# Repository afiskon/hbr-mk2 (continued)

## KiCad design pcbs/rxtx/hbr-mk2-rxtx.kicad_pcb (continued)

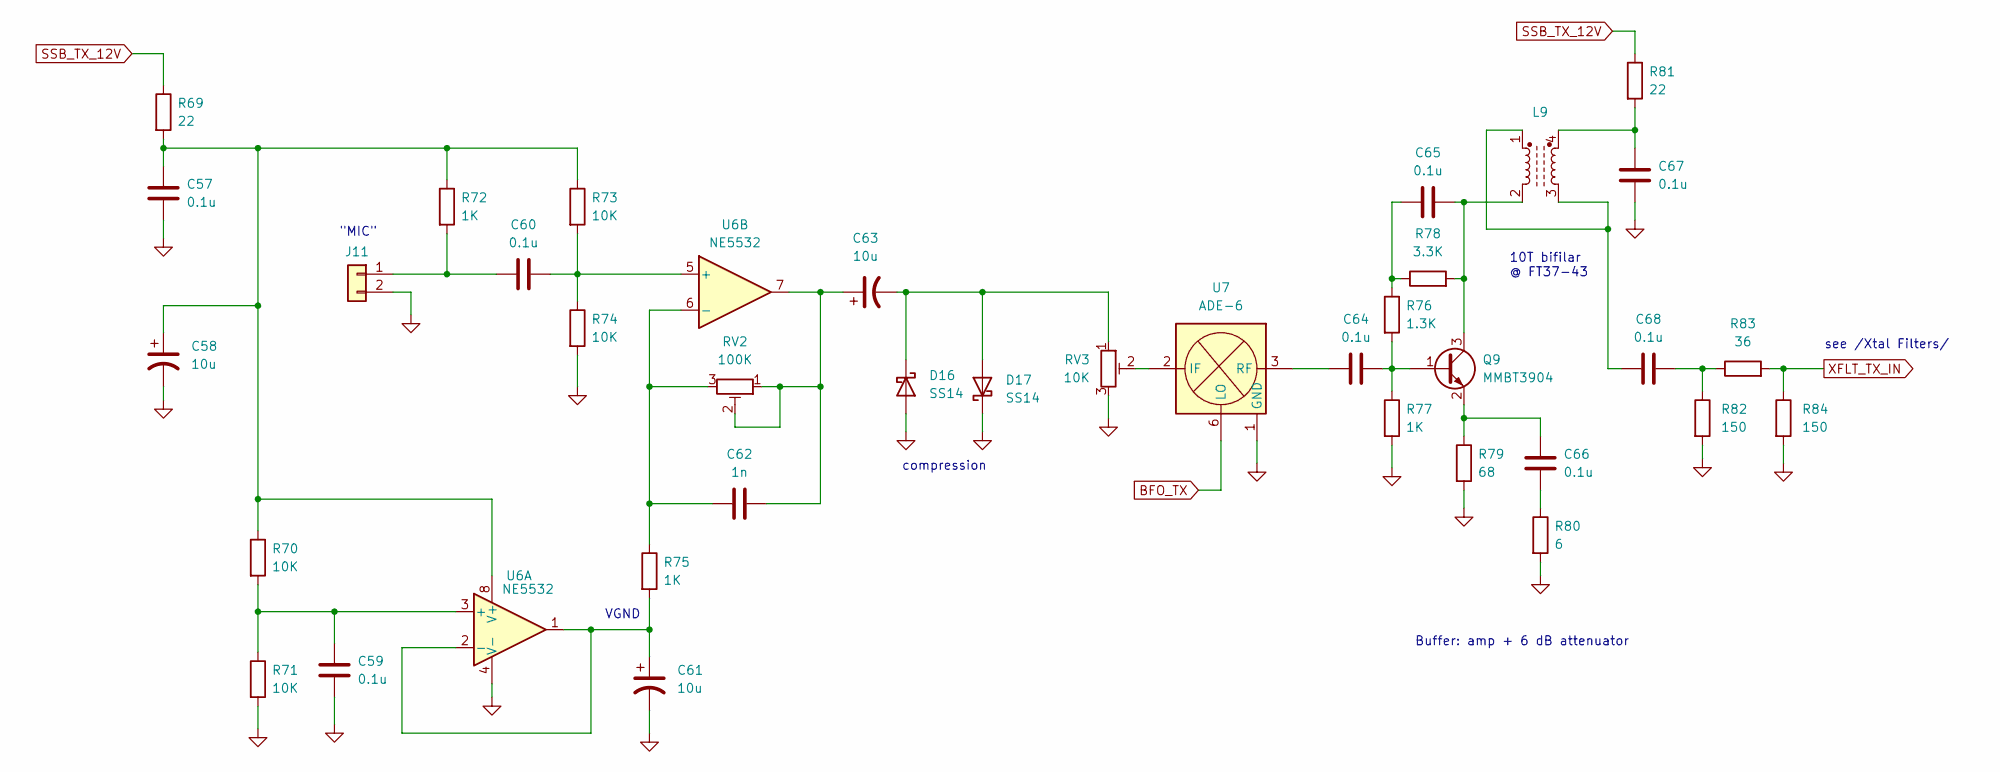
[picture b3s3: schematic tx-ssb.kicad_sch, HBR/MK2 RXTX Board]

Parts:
C57, C59, C60, C64, C65, C66, C67, C68: 0.1u; C_0805_2012Metric_Pad1.18x1.45mm_HandSolder
C58, C61, C63: 10u; CP_Elec_4x5.4
C62: 1n; C_0805_2012Metric_Pad1.18x1.45mm_HandSolder
D16, D17: SS14; D_SMA_Handsoldering
J11: Conn_01x02; PinHeader_1x02_P2.54mm_Vertical
L9: FT37-43; DIP-4_W7.62mm
Q9: MMBT3904; SOT-23
R69, R81: 22; R_0805_2012Metric_Pad1.20x1.40mm_HandSolder
R70, R71, R73, R74: 10K; R_0805_2012Metric_Pad1.20x1.40mm_HandSolder
R72, R75, R77: 1K; R_0805_2012Metric_Pad1.20x1.40mm_HandSolder
R76: 1.3K; R_0805_2012Metric_Pad1.20x1.40mm_HandSolder
R78: 3.3K; R_0805_2012Metric_Pad1.20x1.40mm_HandSolder
R79: 68; R_0805_2012Metric_Pad1.20x1.40mm_HandSolder
R80: 6; R_0805_2012Metric_Pad1.20x1.40mm_HandSolder
R82, R84: 150; R_0805_2012Metric_Pad1.20x1.40mm_HandSolder
R83: 36; R_0805_2012Metric_Pad1.20x1.40mm_HandSolder
RV2: 100K; Potentiometer_Bourns_3296W_Vertical
RV3: 10K; Potentiometer_Bourns_3296W_Vertical
U6: NE5532; SOIC-8_5.23x5.23mm_P1.27mm
U7: ADE-6; Mini-Circuits_CD542_LandPatternPL-052

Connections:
BFO_TX: U7.6 (LO); also elsewhere on the board
GND: C57.2, C58.2, C59.2, C61.2, C67.1, D16.2 (A), D17.1 (K), J11.2, R71.2, R74.2, R77.2, R79.2, R80.2, R82.2, R84.2, RV3.3, U6.4 (V-), U7.1 (GND), U7.4 (GND), U7.5 (GND); also elsewhere on the board
unnamed: C62.2, C63.1, RV2.1, RV2.2, U6.7
unnamed: C65.1, R76.1, R78.1
unnamed: C66.1, R80.1
unnamed: C67.2, L9.4, R81.2
unnamed: C68.1, L9.1, L9.3
unnamed: C68.2, R82.1, R83.1
unnamed: C63.2, D16.1 (K), D17.2 (A), RV3.1
unnamed: C60.1, J11.1, R72.2
unnamed: C64.2, Q9.1 (B), R76.2, R77.1
unnamed: C65.2, L9.2, Q9.3 (C), R78.2
unnamed: C66.2, Q9.2 (E), R79.1
unnamed: C59.1, R70.2, R71.1, U6.3 (+)
unnamed: C61.1, R75.2, U6.1, U6.2 (-)
unnamed: C60.2, R73.2, R74.1, U6.5 (+)
unnamed: C62.1, R75.1, RV2.3, U6.6 (-)
unnamed: C57.1, C58.1, R69.2, R70.1, R72.1, R73.1, U6.8 (V+)
unnamed: RV3.2, U7.2 (IF)
unnamed: C64.1, U7.3 (RF)
SSB_TX_12V: R69.1, R81.1; also elsewhere on the board
XFLT_TX_IN: R83.2, R84.1; also elsewhere on the board

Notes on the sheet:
see /Xtal Filters/
10T bifilar @ FT37-43
Buffer: amp + 6 dB attenuator
VGND
"MIC"
compression

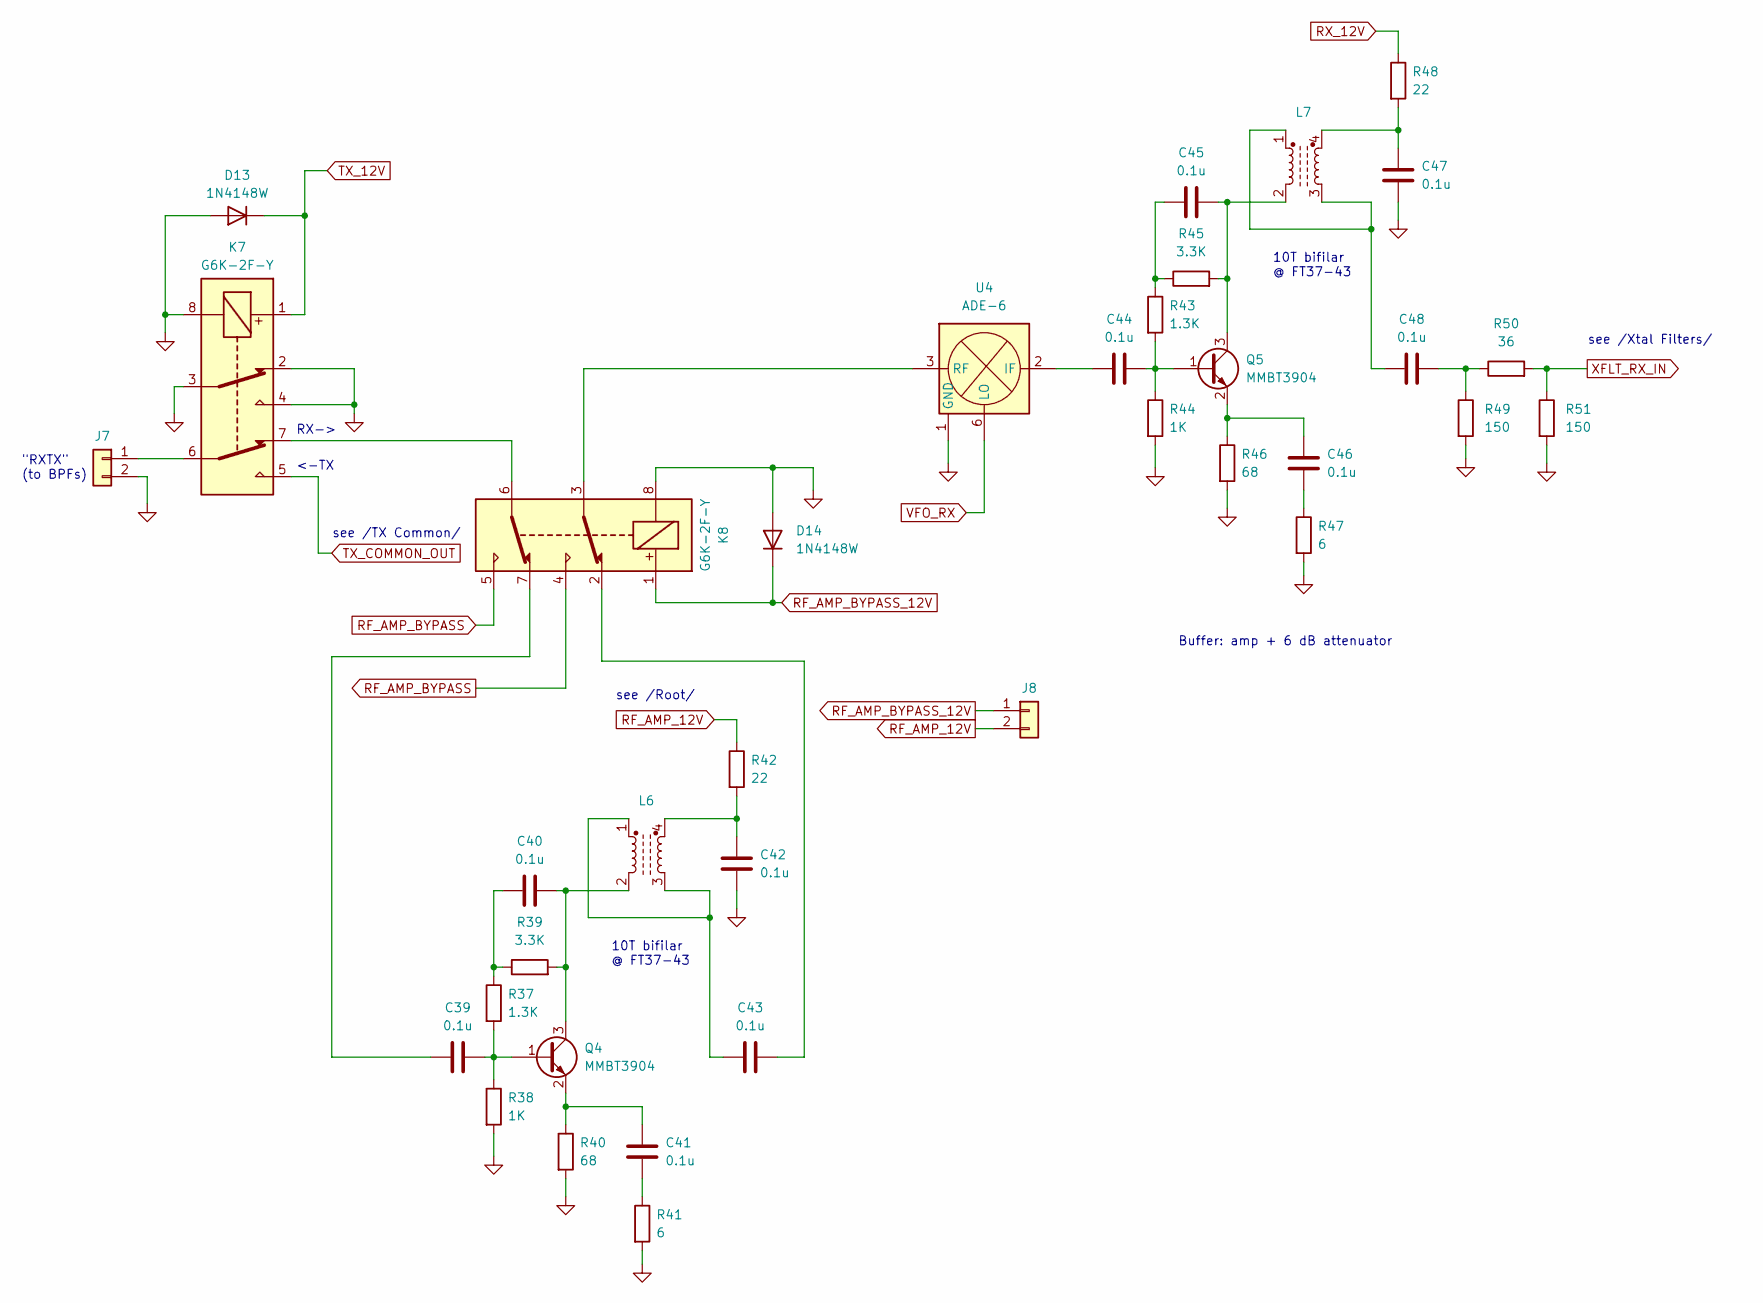
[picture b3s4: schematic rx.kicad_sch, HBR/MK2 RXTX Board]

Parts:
C39, C40, C41, C42, C43, C44, C45, C46, C47, C48: 0.1u; C_0805_2012Metric_Pad1.18x1.45mm_HandSolder
D13, D14: 1N4148W; D_SOD-123
J7, J8: Conn_01x02; PinHeader_1x02_P2.54mm_Vertical
K7, K8: G6K-2F-Y; Relay_DPDT_Omron_G6K-2F-Y
L6, L7: FT37-43; DIP-4_W7.62mm
Q4, Q5: MMBT3904; SOT-23
R37, R43: 1.3K; R_0805_2012Metric_Pad1.20x1.40mm_HandSolder
R38, R44: 1K; R_0805_2012Metric_Pad1.20x1.40mm_HandSolder
R39, R45: 3.3K; R_0805_2012Metric_Pad1.20x1.40mm_HandSolder
R40, R46: 68; R_0805_2012Metric_Pad1.20x1.40mm_HandSolder
R41, R47: 6; R_0805_2012Metric_Pad1.20x1.40mm_HandSolder
R42, R48: 22; R_0805_2012Metric_Pad1.20x1.40mm_HandSolder
R49, R51: 150; R_0805_2012Metric_Pad1.20x1.40mm_HandSolder
R50: 36; R_0805_2012Metric_Pad1.20x1.40mm_HandSolder
U4: ADE-6; Mini-Circuits_CD542_LandPatternPL-052

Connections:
GND: C42.1, C47.1, D13.2 (A), D14.2 (A), J7.2, K7.2, K7.3, K7.4, K7.8, K8.8, R38.2, R40.2, R41.2, R44.2, R46.2, R47.2, R49.2, R51.2, U4.1 (GND), U4.4 (GND), U4.5 (GND); also elsewhere on the board
unnamed: C39.1, K8.7
unnamed: C40.1, R37.1, R39.1
unnamed: C41.1, R41.1
unnamed: C42.2, L6.4, R42.2
unnamed: C43.1, L6.1, L6.3
unnamed: C43.2, K8.2
unnamed: C45.1, R43.1, R45.1
unnamed: C46.1, R47.1
unnamed: C47.2, L7.4, R48.2
unnamed: C48.1, L7.1, L7.3
unnamed: C48.2, R49.1, R50.1
unnamed: J7.1, K7.6
unnamed: K7.7, K8.6
unnamed: C39.2, Q4.1 (B), R37.2, R38.1
unnamed: C40.2, L6.2, Q4.3 (C), R39.2
unnamed: C41.2, Q4.2 (E), R40.1
unnamed: C44.2, Q5.1 (B), R43.2, R44.1
unnamed: C45.2, L7.2, Q5.3 (C), R45.2
unnamed: C46.2, Q5.2 (E), R46.1
unnamed: C44.1, U4.2 (IF)
unnamed: K8.3, U4.3 (RF)
RF_AMP_12V: J8.2, R42.1
RF_AMP_BYPASS: K8.4, K8.5
RF_AMP_BYPASS_12V: D14.1 (K), J8.1, K8.1
RX_12V: R48.1; also elsewhere on the board
TX_12V: D13.1 (K), K7.1; also elsewhere on the board
TX_COMMON_OUT: K7.5; also elsewhere on the board
VFO_RX: U4.6 (LO); also elsewhere on the board
XFLT_RX_IN: R50.2, R51.1; also elsewhere on the board

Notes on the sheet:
see /Xtal Filters/
10T bifilar @ FT37-43
"RXTX" (to BPFs)
RX->
see /TX Common/
see /Root/
Buffer: amp + 6 dB attenuator
<-TX

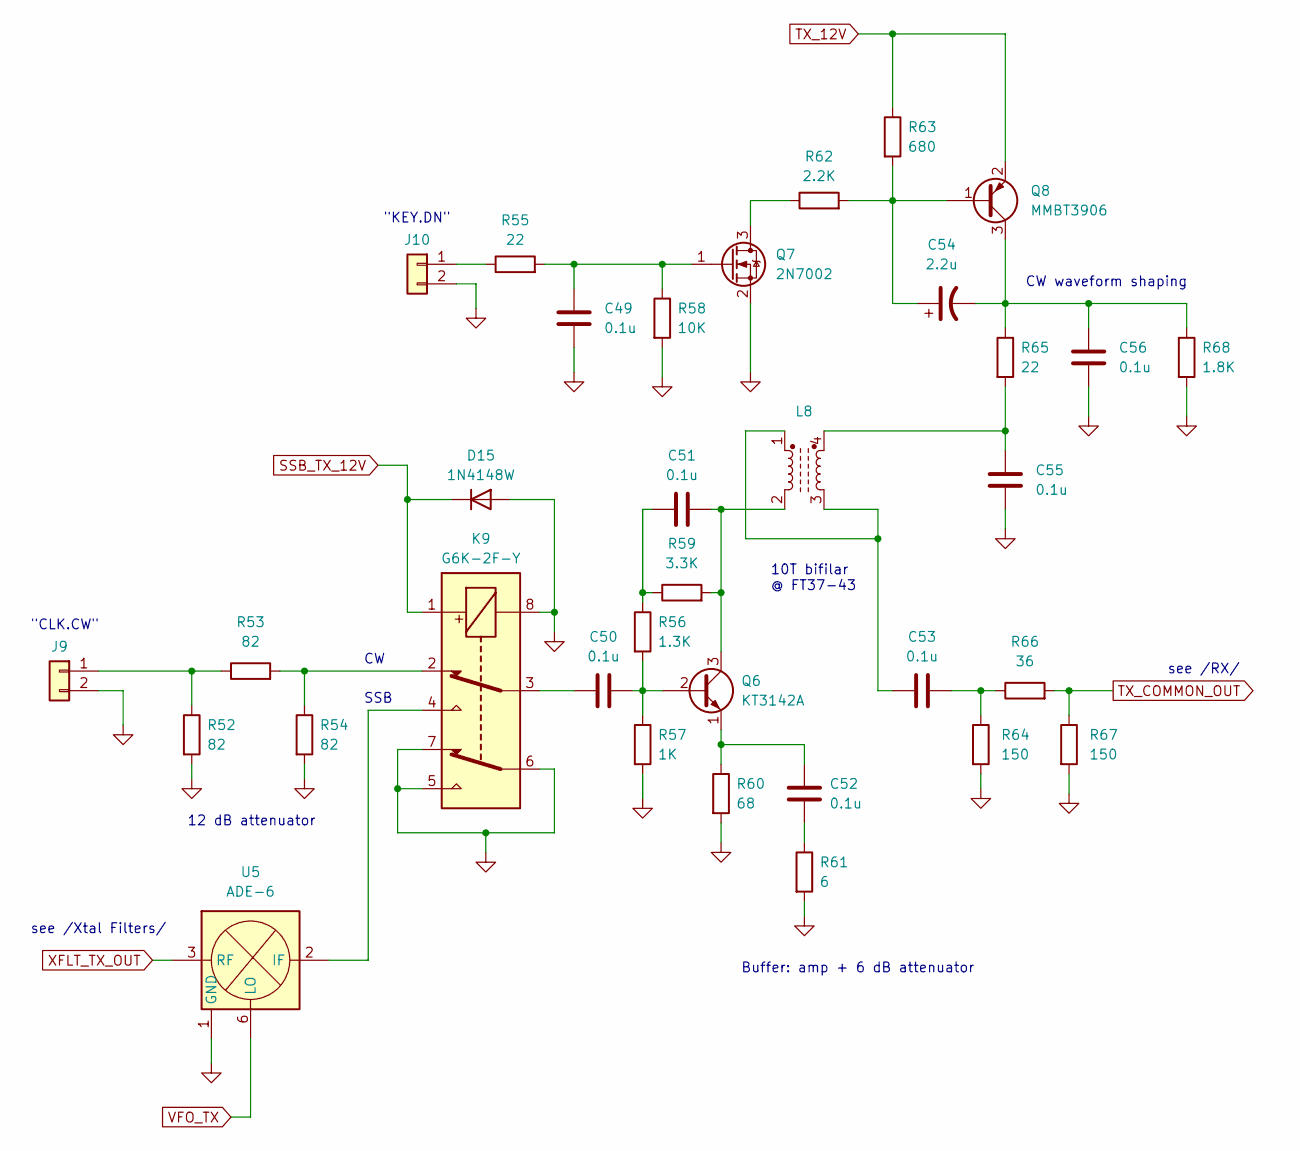
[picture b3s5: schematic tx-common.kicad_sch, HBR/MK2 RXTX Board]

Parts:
C49, C50, C51, C52, C53, C55, C56: 0.1u; C_0805_2012Metric_Pad1.18x1.45mm_HandSolder
C54: 2.2u; CP_Elec_4x5.4
D15: 1N4148W; D_SOD-123
J9, J10: Conn_01x02; PinHeader_1x02_P2.54mm_Vertical
K9: G6K-2F-Y; Relay_DPDT_Omron_G6K-2F-Y
L8: FT37-43; DIP-4_W7.62mm
Q6: KT3142A; TO-18-3
Q7: 2N7002; SOT-23
Q8: MMBT3906; SOT-23
R52, R53, R54: 82; R_0805_2012Metric_Pad1.20x1.40mm_HandSolder
R55, R65: 22; R_0805_2012Metric_Pad1.20x1.40mm_HandSolder
R56: 1.3K; R_0805_2012Metric_Pad1.20x1.40mm_HandSolder
R57: 1K; R_0805_2012Metric_Pad1.20x1.40mm_HandSolder
R58: 10K; R_0805_2012Metric_Pad1.20x1.40mm_HandSolder
R59: 3.3K; R_0805_2012Metric_Pad1.20x1.40mm_HandSolder
R60: 68; R_0805_2012Metric_Pad1.20x1.40mm_HandSolder
R61: 6; R_0805_2012Metric_Pad1.20x1.40mm_HandSolder
R62: 2.2K; R_0805_2012Metric_Pad1.20x1.40mm_HandSolder
R63: 680; R_0805_2012Metric_Pad1.20x1.40mm_HandSolder
R64, R67: 150; R_0805_2012Metric_Pad1.20x1.40mm_HandSolder
R66: 36; R_0805_2012Metric_Pad1.20x1.40mm_HandSolder
R68: 1.8K; R_0805_2012Metric_Pad1.20x1.40mm_HandSolder
U5: ADE-6; Mini-Circuits_CD542_LandPatternPL-052

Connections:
GND: C49.2, C55.2, C56.2, D15.2 (A), J9.2, J10.2, K9.5, K9.6, K9.7, K9.8, Q7.2 (S), R52.2, R54.2, R57.2, R58.2, R60.2, R61.2, R64.2, R67.2, R68.2, U5.1 (GND), U5.4 (GND), U5.5 (GND); also elsewhere on the board
unnamed: C50.1, K9.3
unnamed: C51.1, R56.1, R59.1
unnamed: C52.1, R61.1
unnamed: C53.1, L8.1, L8.3
unnamed: C53.2, R64.1, R66.1
unnamed: C55.1, L8.4, R65.2
unnamed: J9.1, R52.1, R53.1
unnamed: J10.1, R55.1
unnamed: K9.2, R53.2, R54.1
unnamed: C50.2, Q6.2 (B), R56.2, R57.1
unnamed: C51.2, L8.2, Q6.3 (C), R59.2
unnamed: C52.2, Q6.1 (E), R60.1
unnamed: Q7.3 (D), R62.1
unnamed: C49.1, Q7.1 (G), R55.2, R58.1
unnamed: C54.1, Q8.1 (B), R62.2, R63.2
unnamed: C54.2, C56.1, Q8.3 (C), R65.1, R68.1
unnamed: K9.4, U5.2 (IF)
SSB_TX_12V: D15.1 (K), K9.1; also elsewhere on the board
TX_12V: Q8.2 (E), R63.1; also elsewhere on the board
TX_COMMON_OUT: R66.2, R67.1; also elsewhere on the board
VFO_TX: U5.6 (LO); also elsewhere on the board
XFLT_TX_OUT: U5.3 (RF); also elsewhere on the board

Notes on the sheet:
"KEY.DN"
"CLK.CW"
SSB
12 dB attenuator
see /Xtal Filters/
see /RX/
Buffer: amp + 6 dB attenuator
10T bifilar @ FT37-43
CW waveform shaping

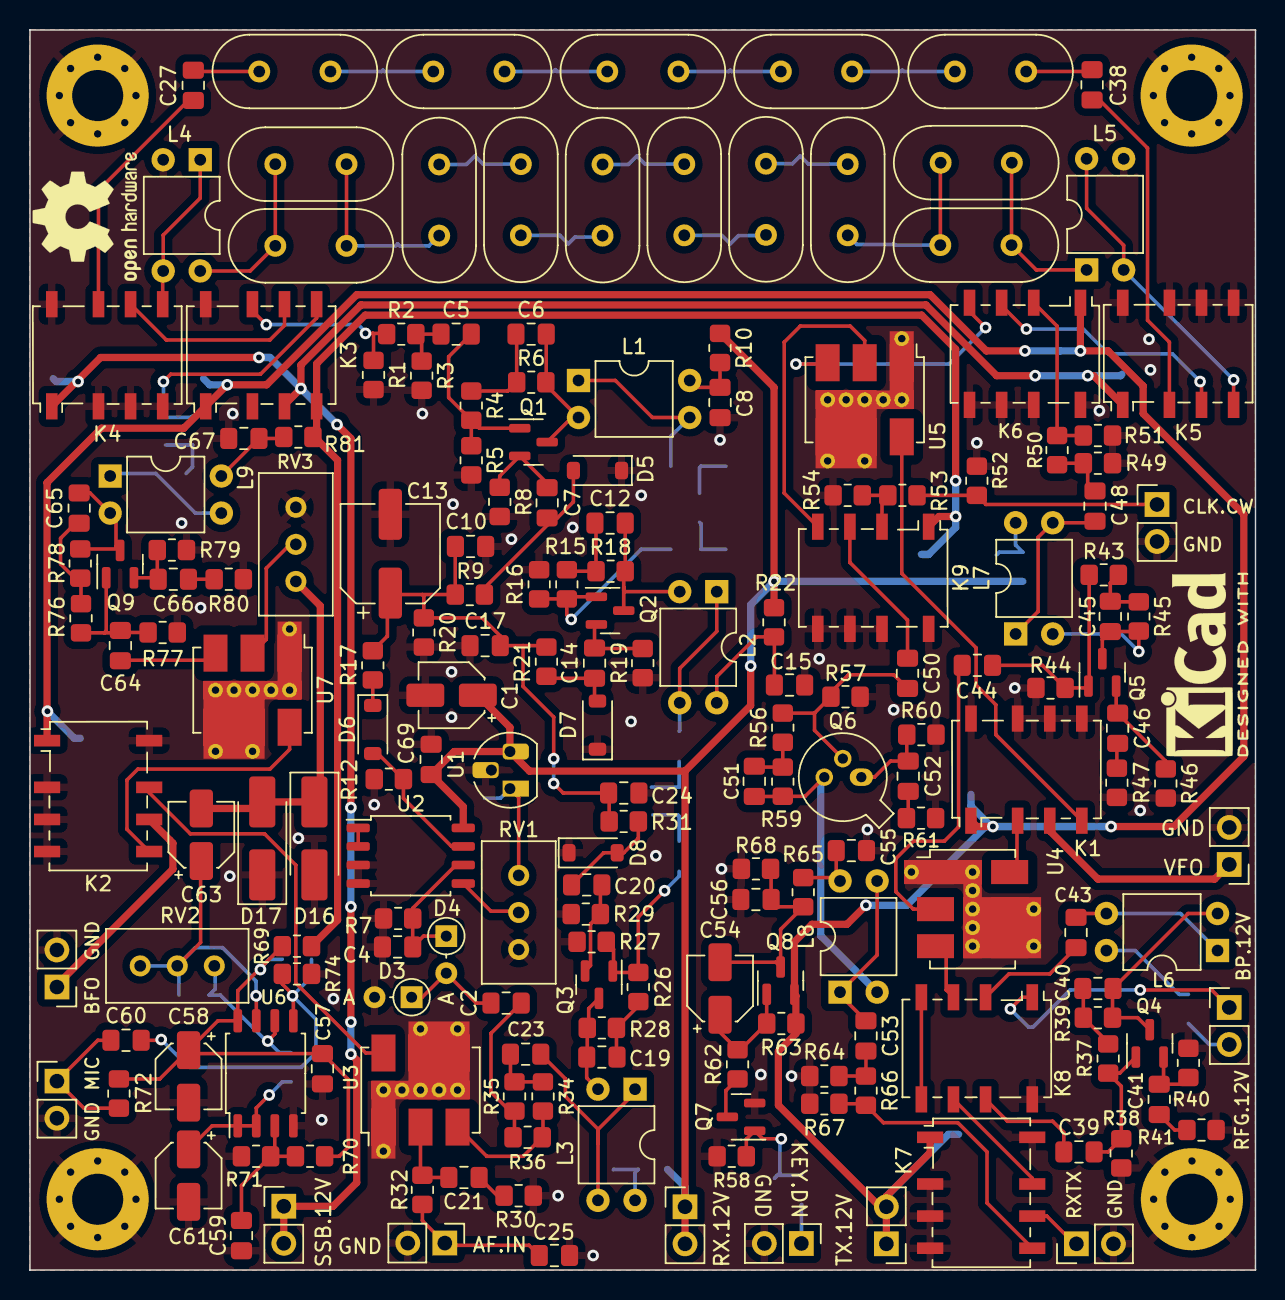
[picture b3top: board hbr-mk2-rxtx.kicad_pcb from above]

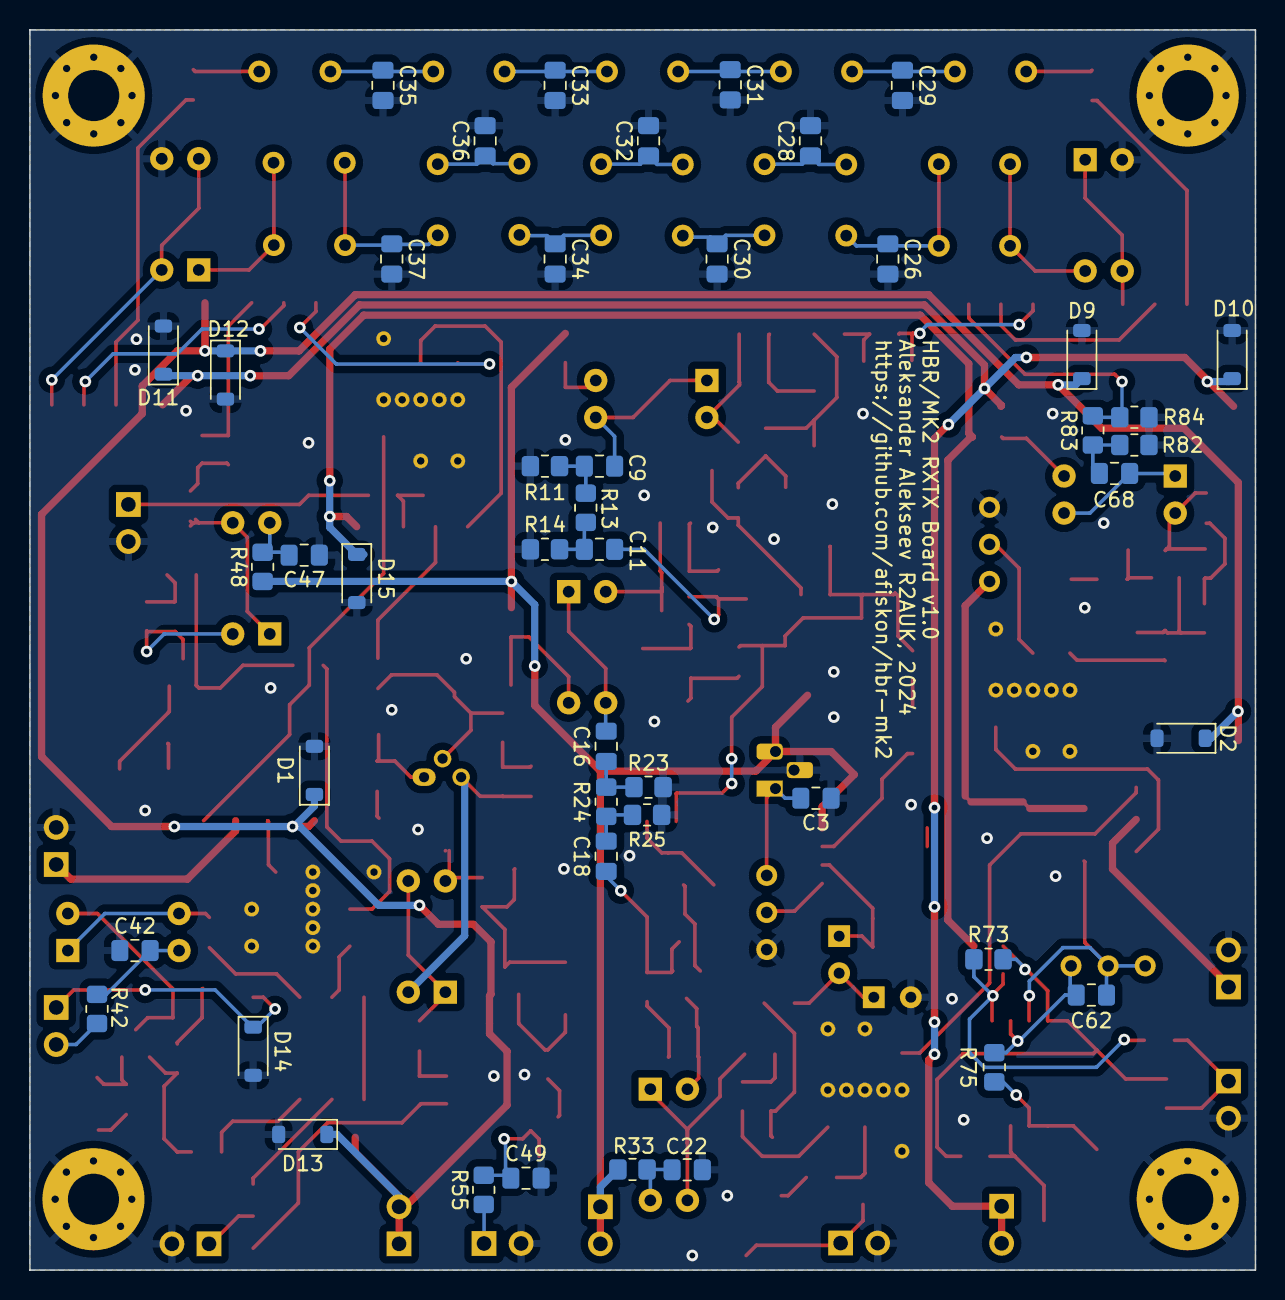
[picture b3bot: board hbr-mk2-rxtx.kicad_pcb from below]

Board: 2 copper layers, 84.0 x 85.0 mm, 239 parts (46 on the bottom side), 136 nets.

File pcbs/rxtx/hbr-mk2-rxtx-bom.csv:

Reference(s),Qty,Value,Footprint
"C1, C58, C61, C63",4,10u,Capacitor_SMD:CP_Elec_4x5.4
"C2, C3, C5, C6, C7, C8, C9, C10, C11, C12, C14, C15, C16, C17, C18, C19, C20, C22, C23, C24, C39, C40, C41, C42, C43, C44, C45, C46, C47, C48, C49, C50, C51, C52, C53, C55, C56, C57, C59, C60, C64, C65, C66, C67, C68, C69",46,0.1u,Capacitor_SMD:C_0805_2012Metric_Pad1.18x1.45mm_HandSolder
C4,1,820p,Capacitor_SMD:C_0805_2012Metric_Pad1.18x1.45mm_HandSolder
C13,1,100u,Capacitor_SMD:CP_Elec_6.3x7.7
C21,1,10n,Capacitor_SMD:C_0805_2012Metric_Pad1.18x1.45mm_HandSolder
C25,1,47n,Capacitor_SMD:C_0805_2012Metric_Pad1.18x1.45mm_HandSolder
"C26, C28, C30, C32, C34, C36, C37",7,56p,Capacitor_SMD:C_0805_2012Metric_Pad1.18x1.45mm_HandSolder
"C27, C29, C31, C33, C35, C38",6,270p,Capacitor_SMD:C_0805_2012Metric_Pad1.18x1.45mm_HandSolder
C54,1,2.2u,Capacitor_SMD:CP_Elec_4x5.4
C62,1,1n,Capacitor_SMD:C_0805_2012Metric_Pad1.18x1.45mm_HandSolder
"D1, D2, D5, D6, D7, D8, D9, D10, D11, D12, D13, D14, D15",13,1N4148W,Diode_SMD:D_SOD-123
"D3, D4",2,1N34/D311,Diode_THT:D_DO-34_SOD68_P2.54mm_Vertical_AnodeUp
"D16, D17",2,SS14,Diode_SMD:D_SMA_Handsoldering
"K1, K2, K3, K4, K5, K6, K7, K8, K9",9,G6K-2F-Y,Relay_SMD:Relay_DPDT_Omron_G6K-2F-Y
"L1, L2, L3, L4, L5, L6, L7, L8, L9",9,FT37-43,Package_DIP:DIP-4_W7.62mm
"Q1, Q2, Q3, Q4, Q5, Q9",6,MMBT3904,Package_TO_SOT_SMD:SOT-23
Q6,1,KT3142A,Package_TO_SOT_THT:TO-18-3
Q7,1,2N7002,Package_TO_SOT_SMD:SOT-23
Q8,1,MMBT3906,Package_TO_SOT_SMD:SOT-23
"R1, R3, R11, R14, R23, R25, R49, R51, R64, R67, R82, R84",12,150,Resistor_SMD:R_0805_2012Metric_Pad1.20x1.40mm_HandSolder
"R2, R13, R24, R50, R66, R83",6,36,Resistor_SMD:R_0805_2012Metric_Pad1.20x1.40mm_HandSolder
"R4, R15, R26",3,820,Resistor_SMD:R_0805_2012Metric_Pad1.20x1.40mm_HandSolder
"R5, R9, R16, R20, R21, R27, R31, R38, R44, R57, R72, R75, R77",13,1K,Resistor_SMD:R_0805_2012Metric_Pad1.20x1.40mm_HandSolder
"R6, R18, R28, R39, R45, R59, R78",7,3.3K,Resistor_SMD:R_0805_2012Metric_Pad1.20x1.40mm_HandSolder
"R7, R12, R58, R70, R71, R73, R74",7,10K,Resistor_SMD:R_0805_2012Metric_Pad1.20x1.40mm_HandSolder
"R8, R19, R29, R40, R46, R60, R79",7,68,Resistor_SMD:R_0805_2012Metric_Pad1.20x1.40mm_HandSolder
"R10, R22, R33",3,100,Resistor_SMD:R_0805_2012Metric_Pad1.20x1.40mm_HandSolder
R17,1,220,Resistor_SMD:R_0805_2012Metric_Pad1.20x1.40mm_HandSolder
"R30, R34, R35, R36",4,51,Resistor_SMD:R_0805_2012Metric_Pad1.20x1.40mm_HandSolder
R32,1,1.5K,Resistor_SMD:R_0805_2012Metric_Pad1.20x1.40mm_HandSolder
"R37, R43, R56, R76",4,1.3K,Resistor_SMD:R_0805_2012Metric_Pad1.20x1.40mm_HandSolder
"R41, R47, R61, R80",4,6,Resistor_SMD:R_0805_2012Metric_Pad1.20x1.40mm_HandSolder
"R42, R48, R55, R65, R69, R81",6,22,Resistor_SMD:R_0805_2012Metric_Pad1.20x1.40mm_HandSolder
"R52, R53, R54",3,82,Resistor_SMD:R_0805_2012Metric_Pad1.20x1.40mm_HandSolder
R62,1,2.2K,Resistor_SMD:R_0805_2012Metric_Pad1.20x1.40mm_HandSolder
R63,1,680,Resistor_SMD:R_0805_2012Metric_Pad1.20x1.40mm_HandSolder
R68,1,1.8K,Resistor_SMD:R_0805_2012Metric_Pad1.20x1.40mm_HandSolder
"RV1, RV3",2,10K,Potentiometer_THT:Potentiometer_Bourns_3296W_Vertical
RV2,1,100K,Potentiometer_THT:Potentiometer_Bourns_3296W_Vertical
U1,1,L78L33,Package_TO_SOT_THT:TO-92_HandSolder
U2,1,LM358,Package_SO:SOIC-8_5.23x5.23mm_P1.27mm
"U3, U4, U5, U7",4,ADE-6,RF_Mini-Circuits:Mini-Circuits_CD542_LandPatternPL-052
U6,1,NE5532,Package_SO:SOIC-8_5.23x5.23mm_P1.27mm
"Y1, Y2, Y3, Y4, Y5, Y6, Y7, Y8, Y9, Y10, Y11, Y12, Y13, Y14, Y15",15,9,Crystal:Crystal_HC49-U_Vertical

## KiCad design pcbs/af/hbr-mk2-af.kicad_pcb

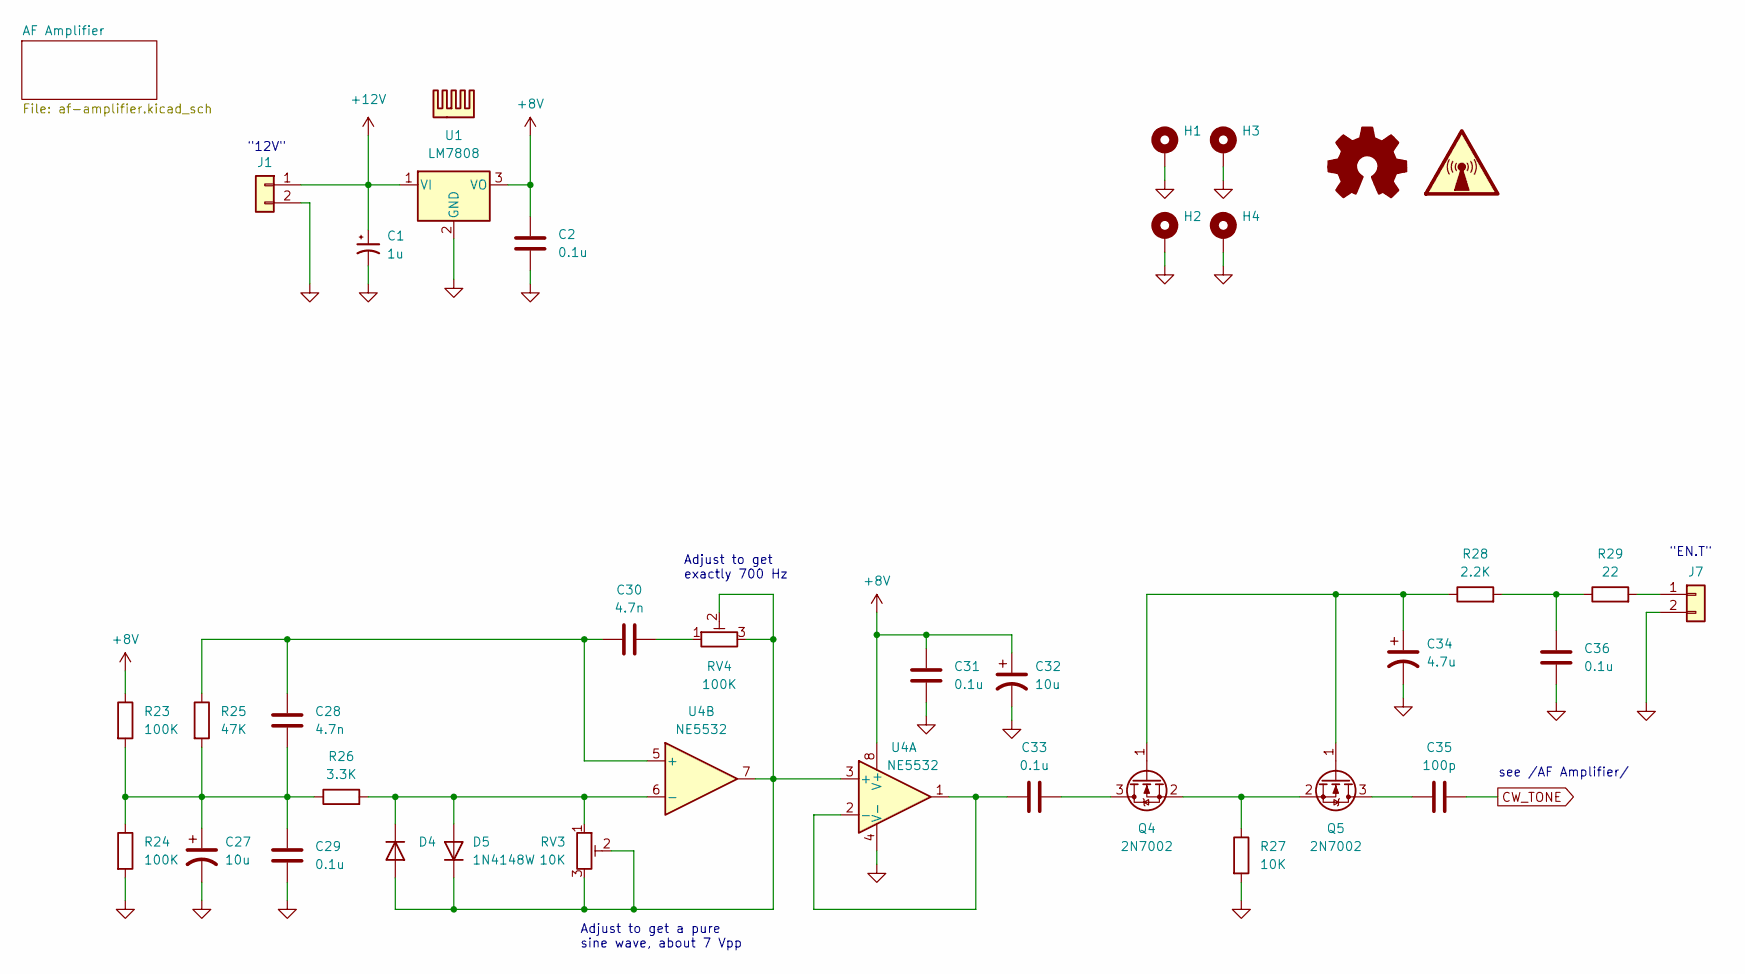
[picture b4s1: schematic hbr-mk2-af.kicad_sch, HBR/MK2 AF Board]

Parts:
C1: 1u; CP_Elec_4x5.4
C2, C29, C31, C33, C36: 0.1u; C_0805_2012Metric_Pad1.18x1.45mm_HandSolder
C27, C32: 10u; CP_Elec_4x5.4
C28, C30: 4.7n; C_0805_2012Metric_Pad1.18x1.45mm_HandSolder
C34: 4.7u; CP_Elec_4x5.4
C35: 100p; C_0805_2012Metric_Pad1.18x1.45mm_HandSolder
D4, D5: 1N4148W; D_SOD-123
H1, H2, H3, H4: MountingHole_Pad; MountingHole_3.5mm_Pad_Via
HS2: Heatsink
J1, J7: Conn_01x02; PinHeader_1x02_P2.54mm_Vertical
Q4, Q5: 2N7002; SOT-23
R23, R24: 100K; R_0805_2012Metric_Pad1.20x1.40mm_HandSolder
R25: 47K; R_0805_2012Metric_Pad1.20x1.40mm_HandSolder
R26: 3.3K; R_0805_2012Metric_Pad1.20x1.40mm_HandSolder
R27: 10K; R_0805_2012Metric_Pad1.20x1.40mm_HandSolder
R28: 2.2K; R_0805_2012Metric_Pad1.20x1.40mm_HandSolder
R29: 22; R_0805_2012Metric_Pad1.20x1.40mm_HandSolder
RV3: 10K; Potentiometer_Bourns_3296W_Vertical
RV4: 100K; Potentiometer_Bourns_3296W_Vertical
SYM1: Logo_Open_Hardware_Small; OSHW-Logo2_9.8x8mm_SilkScreen
SYM2: SYM_Radio_Waves_Large; KiCad-Logo2_5mm_SilkScreen
U1: LM7808; TO-220-3_Vertical
U4: NE5532; SOIC-8_5.23x5.23mm_P1.27mm

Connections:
+8V: C2.1, C31.1, C32.1, R23.1, U1.3 (VO), U4.8 (V+); also elsewhere on the board
+12V: C1.1, J1.1, U1.1 (VI)
CW_TONE: C35.2; also elsewhere on the board
GND: C1.2, C2.2, C27.2, C29.2, C31.2, C32.2, C34.2, C36.2, H1.1, H2.1, H3.1, H4.1, J1.2, J7.2, R24.2, R27.2, U1.2 (GND), U4.4 (V-); also elsewhere on the board
unnamed: C27.1, C28.2, C29.1, R23.2, R24.1, R25.2, R26.1
unnamed: C30.2, RV4.1
unnamed: C36.1, R28.2, R29.1
unnamed: D4.2 (A), D5.1 (K), RV3.2, RV3.3, RV4.2, RV4.3, U4.3 (+), U4.7
unnamed: D4.1 (K), D5.2 (A), R26.2, RV3.1, U4.6 (-)
unnamed: J7.1, R29.2
unnamed: C33.2, Q4.3 (D)
unnamed: C34.1, Q4.1 (G), Q5.1 (G), R28.1
unnamed: Q4.2 (S), Q5.2 (S), R27.1
unnamed: C35.1, Q5.3 (D)
unnamed: C33.1, U4.1, U4.2 (-)
unnamed: C28.1, C30.1, R25.1, U4.5 (+)

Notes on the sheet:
Adjust to get a pure sine wave, about 7 Vpp
Adjust to get exactly 700 Hz
see /AF Amplifier/
"12V"
"EN.T"

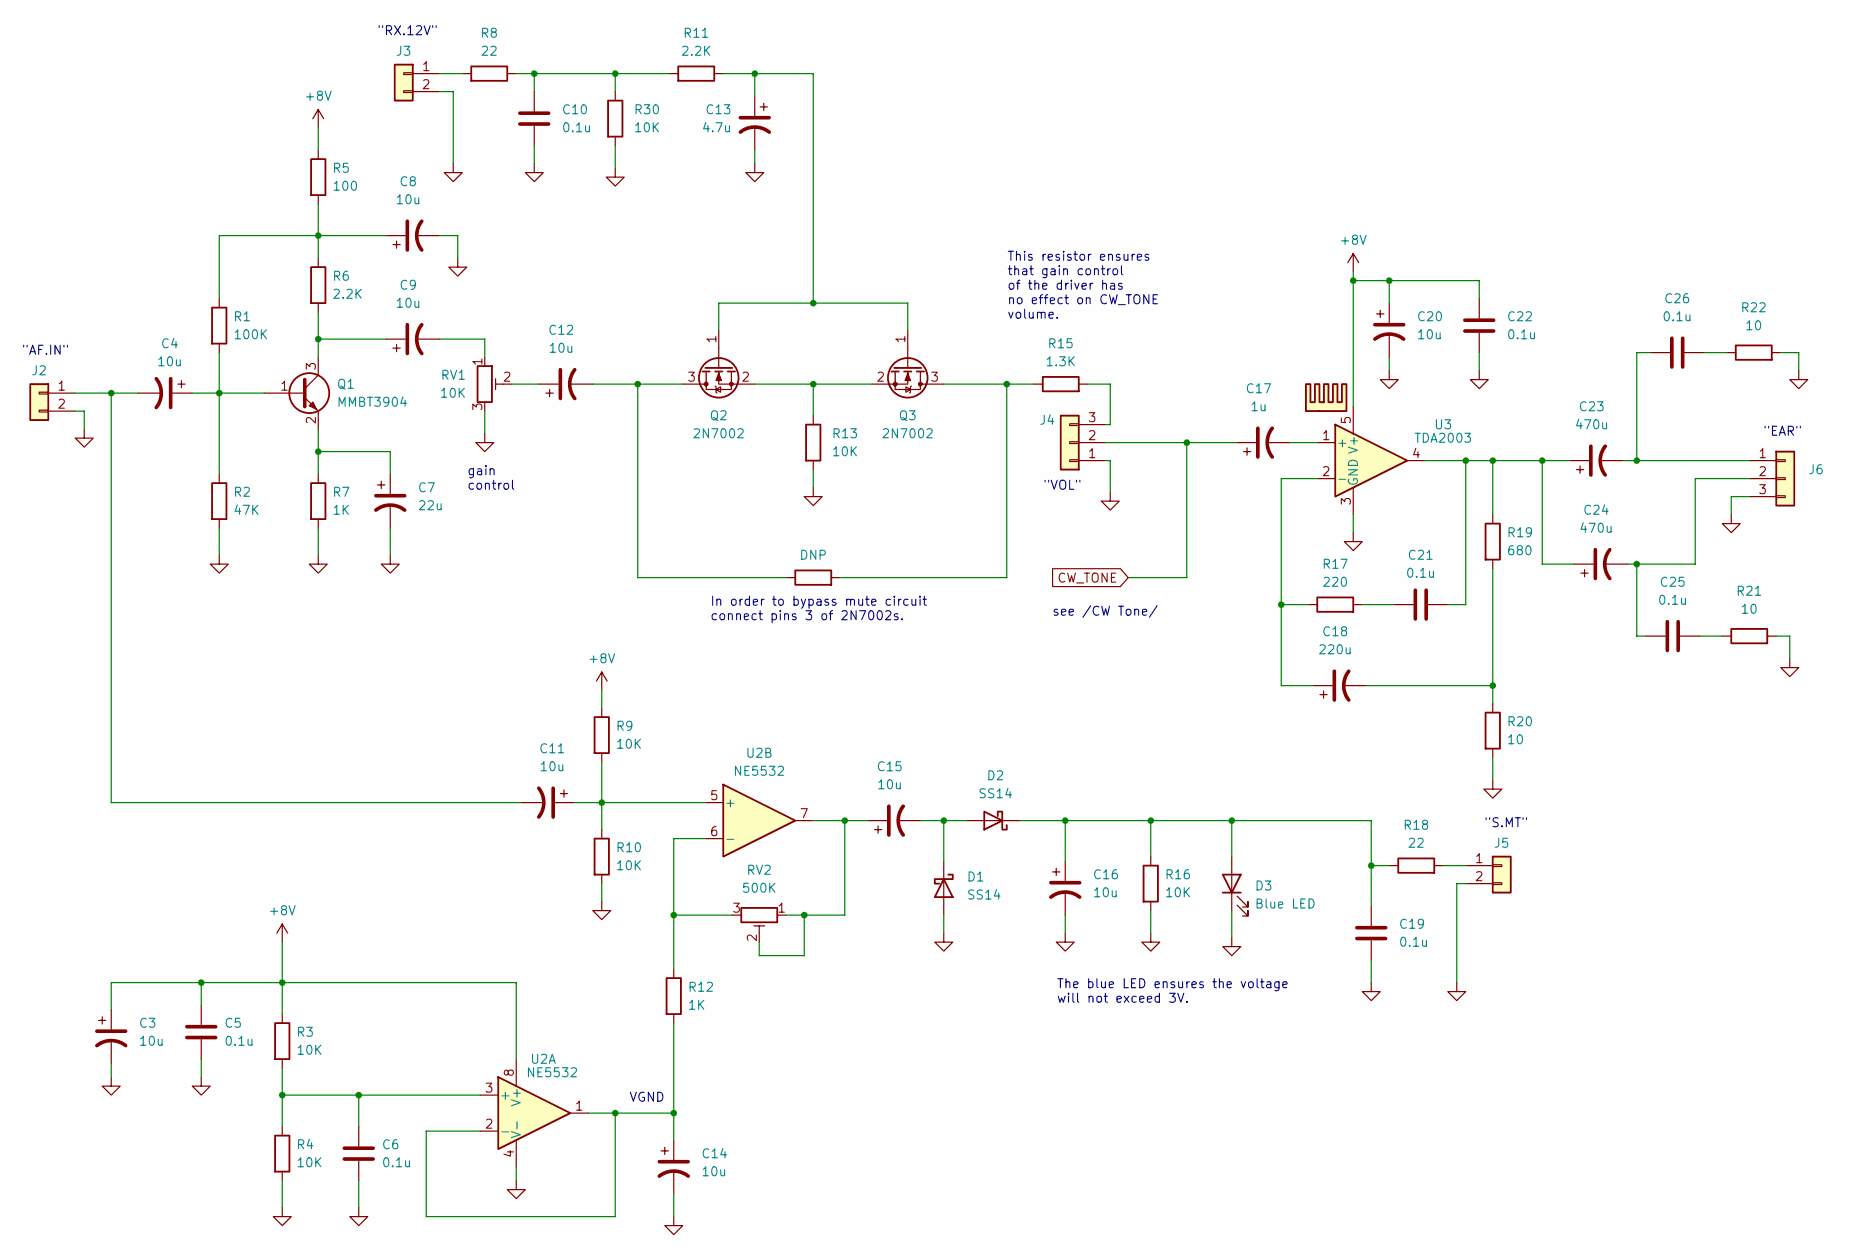
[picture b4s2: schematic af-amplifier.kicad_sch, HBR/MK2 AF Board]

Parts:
C3, C4, C8, C9, C11, C12, C14, C15, C16, C20: 10u; CP_Elec_4x5.4
C5, C6, C10, C19, C21, C22, C25, C26: 0.1u; C_0805_2012Metric_Pad1.18x1.45mm_HandSolder
C7: 22u; CP_Elec_5x5.4
C13: 4.7u; CP_Elec_4x5.4
C17: 1u; CP_Elec_4x5.4
C18: 220u; CP_Elec_8x10.5
C23, C24: 470u; CP_Elec_10x10.5
D1, D2: SS14; D_SMA_Handsoldering
D3: Blue LED; LED_0805_2012Metric_Pad1.15x1.40mm_HandSolder
HS1: Heatsink
J2, J3, J5: Conn_01x02; PinHeader_1x02_P2.54mm_Vertical
J4, J6: Conn_01x03; PinHeader_1x03_P2.54mm_Vertical
Q1: MMBT3904; SOT-23
Q2, Q3: 2N7002; SOT-23
R1: 100K; R_0805_2012Metric_Pad1.20x1.40mm_HandSolder
R2: 47K; R_0805_2012Metric_Pad1.20x1.40mm_HandSolder
R3, R4, R9, R10, R13, R16, R30: 10K; R_0805_2012Metric_Pad1.20x1.40mm_HandSolder
R5: 100; R_0805_2012Metric_Pad1.20x1.40mm_HandSolder
R6, R11: 2.2K; R_0805_2012Metric_Pad1.20x1.40mm_HandSolder
R7, R12: 1K; R_0805_2012Metric_Pad1.20x1.40mm_HandSolder
R8, R18: 22; R_0805_2012Metric_Pad1.20x1.40mm_HandSolder
R14: DNP
R15: 1.3K; R_0805_2012Metric_Pad1.20x1.40mm_HandSolder
R17: 220; R_0805_2012Metric_Pad1.20x1.40mm_HandSolder
R19: 680; R_0805_2012Metric_Pad1.20x1.40mm_HandSolder
R20, R21, R22: 10; R_0805_2012Metric_Pad1.20x1.40mm_HandSolder
RV1: 10K; Potentiometer_Bourns_3296W_Vertical
RV2: 500K; Potentiometer_Bourns_3296W_Vertical
U2: NE5532; SOIC-8_5.23x5.23mm_P1.27mm
U3: TDA2003; TO-220-5_P3.4x3.7mm_StaggerOdd_Lead3.8mm_Vertical

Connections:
+8V: C3.1, C5.1, C20.1, C22.1, R3.1, R5.1, R9.1, U2.8 (V+), U3.5 (V+); also elsewhere on the board
CW_TONE: C17.1, J4.2; also elsewhere on the board
GND: C3.2, C5.2, C6.2, C7.2, C8.2, C10.2, C13.2, C14.2, C16.2, C19.2, C20.2, C22.2, D1.2 (A), D3.1 (K), J2.2, J3.2, J4.1, J5.2, J6.3, R2.2, R4.2, R7.2, R10.2, R13.2, R16.2, R20.2, R21.2, R22.2, R30.2, RV1.3, U2.4 (V-), U3.3 (GND); also elsewhere on the board
unnamed: C8.1, R1.1, R5.2, R6.1
unnamed: C9.2, RV1.1
unnamed: C10.1, R8.1, R11.2, R30.1
unnamed: C12.1, RV1.2
unnamed: C15.1, RV2.1, RV2.2, U2.7
unnamed: C18.2, R19.2, R20.1
unnamed: C21.1, R17.2
unnamed: C21.2, C23.1, C24.1, R19.1, U3.4
unnamed: C25.2, R21.1
unnamed: C26.2, R22.1
unnamed: C15.2, D1.1 (K), D2.2 (A)
unnamed: C16.1, C19.1, D2.1 (K), D3.2 (A), R16.1, R18.1
unnamed: C4.2, C11.2, J2.1
unnamed: J3.1, R8.2
unnamed: J4.3, R15.2
unnamed: J5.1, R18.2
unnamed: C23.2, C26.1, J6.1
unnamed: C24.2, C25.1, J6.2
unnamed: C4.1, Q1.1 (B), R1.2, R2.1
unnamed: C9.1, Q1.3 (C), R6.2
unnamed: C7.1, Q1.2 (E), R7.1
unnamed: C12.2, Q2.3 (D), R14.1
unnamed: C13.1, Q2.1 (G), Q3.1 (G), R11.1
unnamed: Q2.2 (S), Q3.2 (S), R13.1
unnamed: Q3.3 (D), R14.2, R15.1
unnamed: C6.1, R3.2, R4.1, U2.3 (+)
unnamed: C14.1, R12.2, U2.1, U2.2 (-)
unnamed: C11.1, R9.2, R10.1, U2.5 (+)
unnamed: R12.1, RV2.3, U2.6 (-)
unnamed: C17.2, U3.1 (+)
unnamed: C18.1, R17.1, U3.2 (-)

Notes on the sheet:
gain control
"RX.12V"
VGND
In order to bypass mute circuit connect pins 3 of 2N7002s.
This resistor ensures that gain control of the driver has no effect on CW_TONE volume.
The blue LED ensures the voltage will not exceed 3V.
"VOL"
"S.MT"
see /CW Tone/
"EAR"
"AF.IN"
